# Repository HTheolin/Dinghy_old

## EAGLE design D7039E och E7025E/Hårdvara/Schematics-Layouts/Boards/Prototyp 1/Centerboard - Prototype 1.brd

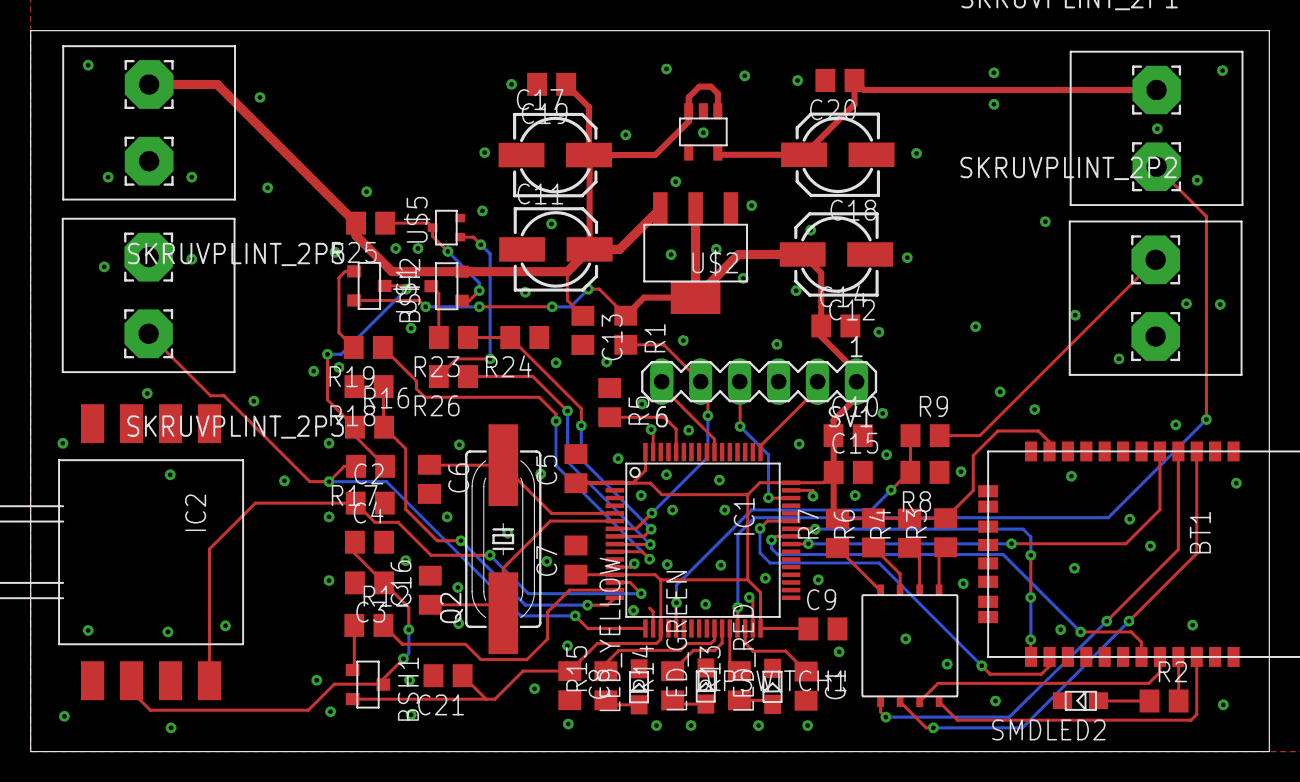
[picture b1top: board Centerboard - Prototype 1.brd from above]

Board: 2 copper layers, 80.8 x 47.0 mm, 62 parts (0 on the bottom side), 49 nets.

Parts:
BSH1, BSH2: ZXMP10A13F; P-CHANNEL
BT1: BLUETOOTH-RN42; RN42
C1: 4u7; C0805
C2: 470pF; C0805
C3: 1uF; C0805
C4: 0.01uF; C0805
C5, C7, C8, C9, C10, C13, C14, C15, C19, C20: 100n; C0805
C6, C16: 25p; C0805
C11, C12, C17, C18: 10u; 153CLV-0505
C21: 1u; C0805
DIPSWITCH1: DIPSWITCH_4P; DIPSWITCH4P
IC1: STM32F401RBT; LQFP64
IC2: MP3V5010; CASE1351
IC3: TPS76150DBVT
LED_GREEN: SMD_LED; SMD_LED_CUSTOM
LED_RED: SMD_LED; SMD_LED_CUSTOM
LED_YELLOW: SMD_LED; SMD_LED_CUSTOM
Q2: 18p; HC49UP
R1, R5, R25: 10k; R0805
R2, R13, R14, R15: 220; R0805
R3, R4, R6, R7, R8, R12, R19, R26: 1k; R0805
R9: 680; R0805
R16, R17, R18: 350; R0805
R23: 6.8k; R0805
R24: 3.3k; R0805
SKRUVPLINT_2P1, SKRUVPLINT_2P2, SKRUVPLINT_2P3, SKRUVPLINT_2P5: SKRUVPLINT_2P
SMDLED2: SMD_LED; SMD_LED_CUSTOM
SV1: MA06-1
U$1: ZXMP10A13F; P-CHANNEL
U$2: LM1117; SOT-223
U$5: SI1330EDL; SOT-323

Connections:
+3V3: BSH1.SOURCE, BSH2.SOURCE, BT1.11, C5.1, C7.1, C8.1, C9.1, C10.1, C12.+, C14.1, C15.1, C21.1, IC1.1, IC1.13, IC1.19, IC1.32, IC1.48, IC1.64, R1.1, R3.2, R4.2, R6.2, R7.2, SV1.1, U$2.OUTPUT, U$2.VOUT
+5V: C18.+, C20.1, IC3.OUT, SKRUVPLINT_2P1.4
BATMEAS_ON/OFF: IC1.9, R26.1
BAT_MEAS: IC1.8, R23.1, R24.2
BT1_CONNSTAT: BT1.19, IC1.41
BT1_GPIO3: BT1.20, DIPSWITCH1.T2
BT1_GPIO4: BT1.22, DIPSWITCH1.T1
BT1_GPIO6: BT1.3, DIPSWITCH1.T3
BT1_GPIO7: BT1.4, DIPSWITCH1.T4
BT1_RESET: BT1.5, IC1.40
BT1_USART1_RX: BT1.14, IC1.43
BT1_USART1_TX: BT1.13, IC1.42
GND: BT1.1, BT1.12, BT1.15, BT1.16, BT1.17, BT1.18, BT1.28, BT1.29, BT1.31, BT1.32, BT1.33, BT1.34, C1.2, C2.2, C3.2, C4.2, C5.2, C6.2, C7.2, C8.2, C9.2, C10.2, C11.-, C12.-, C13.2, C14.2, C15.2, C16.2, C17.-, C18.-, C19.2, C20.2, C21.2, IC1.12, IC1.18, IC1.31, IC1.47, IC1.63, IC2.P$3, IC3.GND, LED_GREEN.2, LED_RED.2, LED_YELLOW.2, R5.1, R8.1, R18.2, R24.1, SKRUVPLINT_2P2.3, SKRUVPLINT_2P3.3, SKRUVPLINT_2P5.4, SMDLED2.2, SV1.3, U$2.GND, U$5.SOURCE
GPIO_ULTRA_INPUT: IC1.21, R8.2, R9.1
GPIO_ULTRA_TRIGGER: IC1.29, SKRUVPLINT_2P1.3
LED_GREEN: IC1.27, R14.2
LED_RED: IC1.28, R13.2
LED_YELLOW: IC1.26, R15.2
unnamed: C1.1, IC1.30
unnamed: IC1.60, R5.2
unnamed: LED_RED.1, R13.1
unnamed: BT1.21, R2.2
unnamed: DIPSWITCH1.B1, R3.1
unnamed: DIPSWITCH1.B2, R4.1
unnamed: DIPSWITCH1.B3, R6.1
unnamed: C6.1, IC1.5, Q2.2
unnamed: C16.1, IC1.6, Q2.1
unnamed: DIPSWITCH1.B4, R7.1
unnamed: R2.1, SMDLED2.1
unnamed: R9.2, SKRUVPLINT_2P2.4
unnamed: BSH1.DRAIN, C3.1, C4.1, IC2.P$2
unnamed: BSH1.GATE, R12.1
unnamed: LED_GREEN.1, R14.1
unnamed: LED_YELLOW.1, R15.1
unnamed: BSH2.DRAIN, R16.1, R17.1
unnamed: BSH2.GATE, R19.2
unnamed: C11.+, C13.1, C17.+, C19.1, IC3.EN, IC3.IN, R25.2, SKRUVPLINT_2P5.3, U$1.SOURCE, U$2.INPUT
unnamed: R23.2, U$1.DRAIN
unnamed: R25.1, U$1.GATE, U$5.DRAIN
unnamed: R26.2, U$5.GATE
NRST: IC1.7, R1.2, SV1.5
PRESSURE_ADC: C2.1, IC1.14, IC2.P$4
PRESSURE_ON/OFF: IC1.15, R12.2
STRAIN_ADC1: IC1.16, R16.2, R18.1
STRAIN_ADC2: IC1.17, R17.2, SKRUVPLINT_2P3.4
STRAIN_ON/OFF: IC1.10, R19.1
SWCLK: IC1.49, SV1.2
SWDIO: IC1.46, SV1.4
SWO: IC1.55, SV1.6

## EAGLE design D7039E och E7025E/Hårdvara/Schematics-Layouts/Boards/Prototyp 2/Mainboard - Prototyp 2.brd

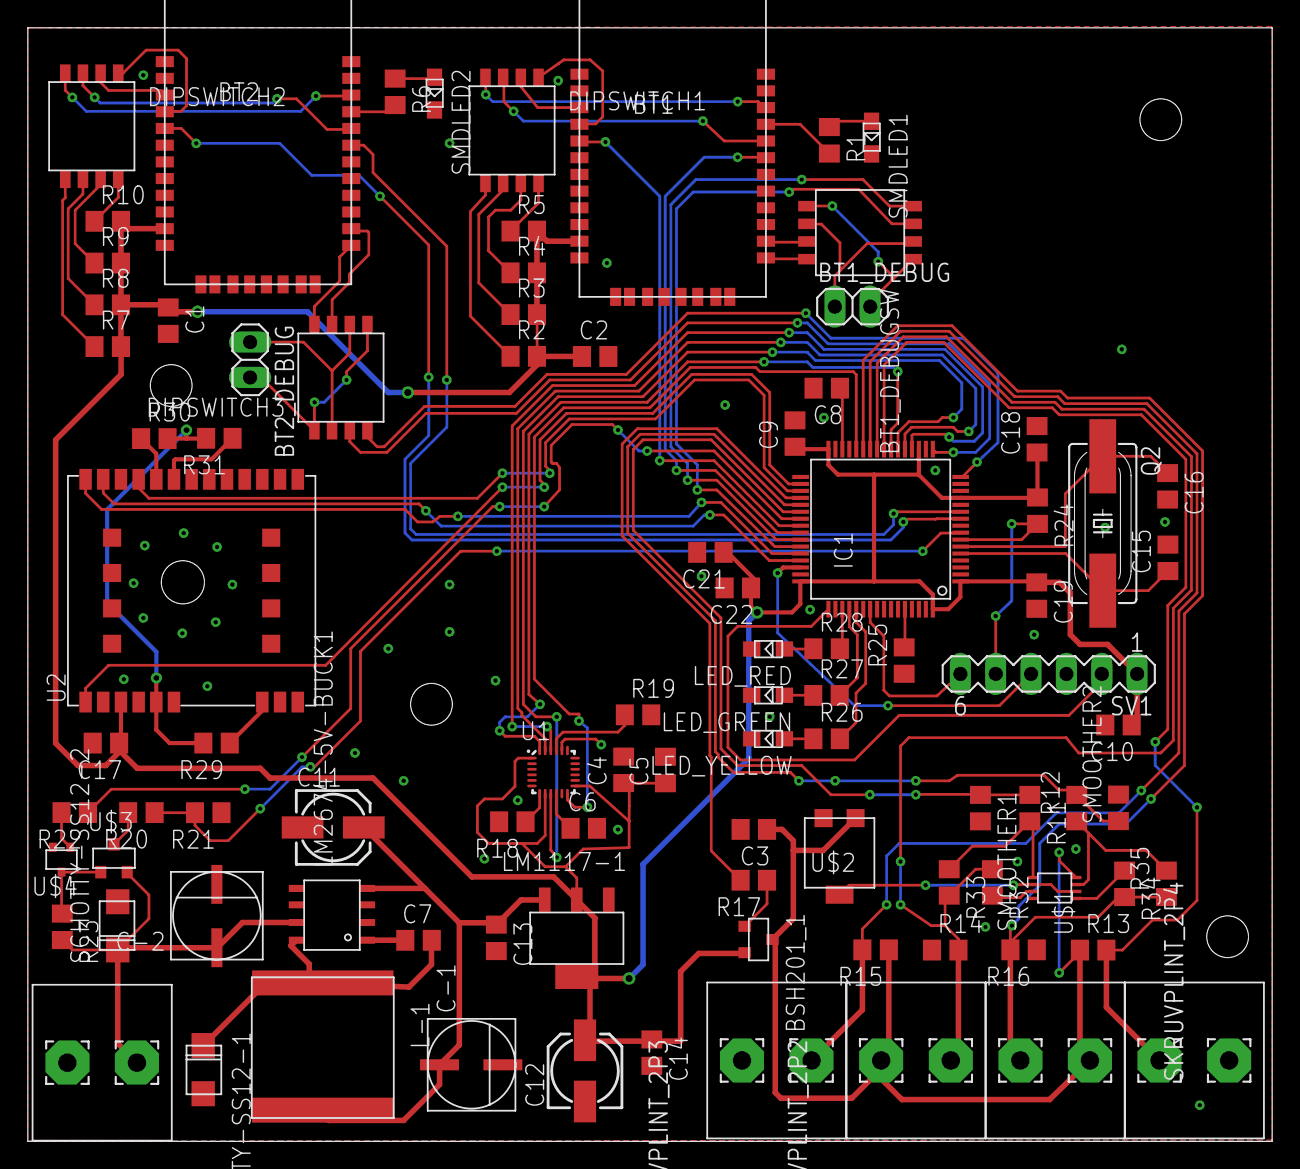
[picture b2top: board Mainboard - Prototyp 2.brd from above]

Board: 2 copper layers, 89.4 x 80.0 mm, 93 parts (0 on the bottom side), 91 nets.

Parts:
BSH201_1: BSH201; P-CHANNEL
BT1, BT2: BLUETOOTH-RN42; RN42
BT1_DEBUG, BT2_DEBUG: 1X02
BT1_DEBUGSW: DIPSWITCH_4P; DIPSWITCH4P
C1, C2, C3, C4, C6, C9, C10, C13, C14, C17, C18, C19, C22: 100n; C0805
C5: 10n; C0805
C7: 0.01uF; C0805
C8: 4u7; C0805
C11, C12: 10u; 153CLV-0505
C15, C16: 25p; C0805
C21: 1u; C0805
C-1, C-2: 100uF; CAP-6.3MM-DIA
DIPSWITCH1, DIPSWITCH2, DIPSWITCH3: DIPSWITCH_4P; DIPSWITCH4P
IC1: STM32F401RBT; LQFP64
L-1: 55uH; INDUCTOR
LED_GREEN: SMD_LED; SMD_LED_CUSTOM
LED_RED: SMD_LED; SMD_LED_CUSTOM
LED_YELLOW: SMD_LED; SMD_LED_CUSTOM
LM1117-1: LM1117
LM2674-5V-BUCK1: LM2674-5VBUCK; LM2674
Q2: 18p; HC49UP
R1, R6, R26, R27, R28: 220; R0805
R2, R3, R4, R5, R7, R8, R9, R10, R11, R12, R22, R32, R34: 1k; R0805
R13, R15: 68; R0805
R14, R16: 4.7k; R0805
R17: 150; R0805
R18, R19: 0; R0805
R20: 6.8k; R0805
R21: 3.3k; R0805
R23, R24, R25, R29, R33, R35: 10k; R0805
R30, R31: 2k2; R0805
SCHOTTY-SS12-1, SCHOTTY-SS12-2: SCHOTTY-SS12; SCHOTTY
SKRUVPLINT_2P1, SKRUVPLINT_2P2, SKRUVPLINT_2P3, SKRUVPLINT_2P4, SKRUVPLINT_2P5: SKRUVPLINT_2P
SMDLED1, SMDLED2: SMD_LED; SMD_LED_CUSTOM
SMOOTHER1, SMOOTHER2: 1n; C0805
SV1: MA06-1
U1: MPU-9250; QFN40P300X300X105-25N
U2: A2235-H; XCVR_A2235-H
U$1: TLV7256; VSSOP
U$2: TS53YL; POT
U$3: ZXMP10A13F; P-CHANNEL
U$4: SI1330EDL; SOT-323

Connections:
1V8_VOUT: R29.2, R30.2, R31.2, U2.5
+3V3: BSH201_1.SOURCE, BT1.11, BT2.11, C1.1, C2.1, C4.1, C5.1, C9.1, C10.1, C12.+, C14.1, C17.1, C18.1, C19.1, C21.1, C22.1, IC1.1, IC1.13, IC1.19, IC1.32, IC1.48, IC1.64, LM1117-1.OUTPUT, LM1117-1.OUTPUT2, R2.2, R3.2, R4.2, R5.2, R7.2, R8.2, R9.2, R10.2, R24.1, SV1.1, U1.1, U1.8, U1.13, U2.3
+5V: C11.+, C13.1, C-1.+, L-1.2, LM1117-1.INPUT, LM2674-5V-BUCK1.4
BATMEAS_TOGGLE: IC1.39, R22.1
BATSUP: C-2.+, LM2674-5V-BUCK1.7, R23.2, SCHOTTY-SS12-2.-, SKRUVPLINT_2P5.3, U$3.SOURCE
BAT_MEAS: IC1.8, R20.1, R21.2
BT1_CONNSTATUS: BT1.19, IC1.41
BT1_DEBUGRX: BT1_DEBUG.2, BT1_DEBUGSW.B1, BT1_DEBUGSW.T4
BT1_DEBUGTX: BT1_DEBUG.1, BT1_DEBUGSW.B2, BT1_DEBUGSW.T3
BT1_GPIO3: BT1.20, DIPSWITCH1.T2
BT1_GPIO4: BT1.22, DIPSWITCH1.T1
BT1_GPIO6: BT1.3, DIPSWITCH1.T3
BT1_GPIO7: BT1.4, DIPSWITCH1.T4
BT1_RESET: BT1.5, IC1.40
BT1_RX: BT1.13, BT1_DEBUGSW.B4
BT1_TX: BT1.14, BT1_DEBUGSW.B3
BT2_CONNSTATUS: BT2.19, IC1.11
BT2_DEBUGRX: BT2_DEBUG.2, DIPSWITCH3.B1, DIPSWITCH3.T4
BT2_DEBUGTX: BT2_DEBUG.1, DIPSWITCH3.B2, DIPSWITCH3.T3
BT2_GPIO3: BT2.20, DIPSWITCH2.T2
BT2_GPIO4: BT2.22, DIPSWITCH2.T1
BT2_GPIO6: BT2.3, DIPSWITCH2.T3
BT2_GPIO7: BT2.4, DIPSWITCH2.T4
BT2_RESET: BT2.5, IC1.10
BT2_RX: BT2.13, DIPSWITCH3.B4
BT2_TX: BT2.14, DIPSWITCH3.B3
GND: BT1.1, BT1.12, BT1.15, BT1.16, BT1.17, BT1.18, BT1.28, BT1.29, BT1.31, BT1.32, BT1.33, BT1.34, BT2.1, BT2.12, BT2.15, BT2.16, BT2.17, BT2.18, BT2.28, BT2.29, BT2.31, BT2.32, BT2.33, BT2.34, C1.2, C2.2, C3.2, C4.2, C5.2, C6.2, C8.2, C9.2, C10.2, C11.-, C12.-, C13.2, C14.2, C15.2, C16.2, C17.2, C18.2, C19.2, C21.2, C22.2, C-1.-, C-2.-, IC1.12, IC1.18, IC1.31, IC1.47, IC1.63, LED_GREEN.2, LED_RED.2, LED_YELLOW.2, LM1117-1.ADJ/GND, LM2674-5V-BUCK1.6, R14.1, R16.1, R18.2, R19.2, R21.1, R25.1, SCHOTTY-SS12-1.+, SCHOTTY-SS12-2.+, SKRUVPLINT_2P1.4, SKRUVPLINT_2P3.4, SKRUVPLINT_2P5.4, SMDLED1.2, SMDLED2.2, SMOOTHER1.2, SMOOTHER2.2, SV1.3, U1.11, U1.18, U1.20, U2.6, U2.9, U2.20, U2.23, U2.24, U2.25, U2.26, U2.27, U2.28, U2.29, U2.30, U$1.P$4, U$2.P$1_A, U$4.SOURCE
GPS_NRST: IC1.34, U2.1
GPS_TOGGLE: IC1.35, U2.19
IMU_INT: IC1.28, U1.12
LED_GREEN: IC1.52, R27.2
LED_RED: IC1.51, R28.2
LED_YELLOW: IC1.53, R26.2
MCURX1_BT1TX: BT1_DEBUGSW.T2, IC1.43
MCURX2_BT2TX: DIPSWITCH3.T2, IC1.17
MCURX6_GPSTX: IC1.45, U2.21
MCUTX1_BT1RX: BT1_DEBUGSW.T1, IC1.42
MCUTX2_BT2RX: DIPSWITCH3.T1, IC1.16
MCUTX6_GPSRX: IC1.44, U2.22
unnamed: BT1.21, R1.2
unnamed: DIPSWITCH1.B1, R2.1
unnamed: DIPSWITCH1.B2, R3.1
unnamed: DIPSWITCH1.B3, R4.1
unnamed: DIPSWITCH1.B4, R5.1
unnamed: BT2.21, R6.2
unnamed: DIPSWITCH2.B1, R7.1
unnamed: DIPSWITCH2.B2, R8.1
unnamed: DIPSWITCH2.B3, R9.1
unnamed: DIPSWITCH2.B4, R10.1
unnamed: R6.1, SMDLED2.1
unnamed: R1.1, SMDLED1.1
unnamed: R11.2, R33.1, U$1.P$1
unnamed: U$1.P$2, U$1.P$6, U$2.P$2_B
unnamed: R12.1, R35.2, U$1.P$7
unnamed: R29.1, U2.7
unnamed: R30.1, U2.18
unnamed: BSH201_1.GATE, R17.1
unnamed: C6.1, U1.10
unnamed: R18.1, U1.7
unnamed: R19.1, U1.21
unnamed: C7.1, LM2674-5V-BUCK1.1
unnamed: R20.2, U$3.DRAIN
unnamed: R22.2, U$4.GATE
unnamed: R23.1, U$3.GATE, U$4.DRAIN
unnamed: C8.1, IC1.30
unnamed: IC1.60, R25.2
unnamed: C15.1, IC1.5, Q2.2
unnamed: C16.1, IC1.6, Q2.1
unnamed: LED_YELLOW.1, R26.1
unnamed: LED_GREEN.1, R27.1
unnamed: R31.1, U2.17
unnamed: LED_RED.1, R28.1
unnamed: R32.2, U$1.P$3
unnamed: R34.1, U$1.P$5
NRST: IC1.7, R24.2, SV1.5
OPTO1_DIODE: IC1.24, R13.2, SKRUVPLINT_2P1.3
OPTO1_OUT: IC1.38, R11.1, SMOOTHER1.1
OPTO1_TRAN: IC1.25, R14.2, R32.1, R33.2, SKRUVPLINT_2P2.3
OPTO2_DIODE: IC1.26, R15.2, SKRUVPLINT_2P3.3
OPTO2_OUT: IC1.37, R12.2, SMOOTHER2.1
OPTO2_TRAN: IC1.27, R16.2, R34.2, R35.1, SKRUVPLINT_2P4.3
OPTO_TOGGLE: IC1.36, R17.2
OPTO_VDD: BSH201_1.DRAIN, C3.1, R13.1, R15.1, SKRUVPLINT_2P2.4, SKRUVPLINT_2P4.4, U$1.P$8, U$2.P$3_C
SPI1_MISO: IC1.22, U1.9
SPI1_MOSI: IC1.23, U1.24
SPI1_NSS: IC1.20, U1.22
SPI1_SCK: IC1.21, U1.23
SWCLK: IC1.49, SV1.2
SWDIO: IC1.46, SV1.4
SWO: IC1.55, SV1.6
VOUT: C7.2, L-1.1, LM2674-5V-BUCK1.8, SCHOTTY-SS12-1.-

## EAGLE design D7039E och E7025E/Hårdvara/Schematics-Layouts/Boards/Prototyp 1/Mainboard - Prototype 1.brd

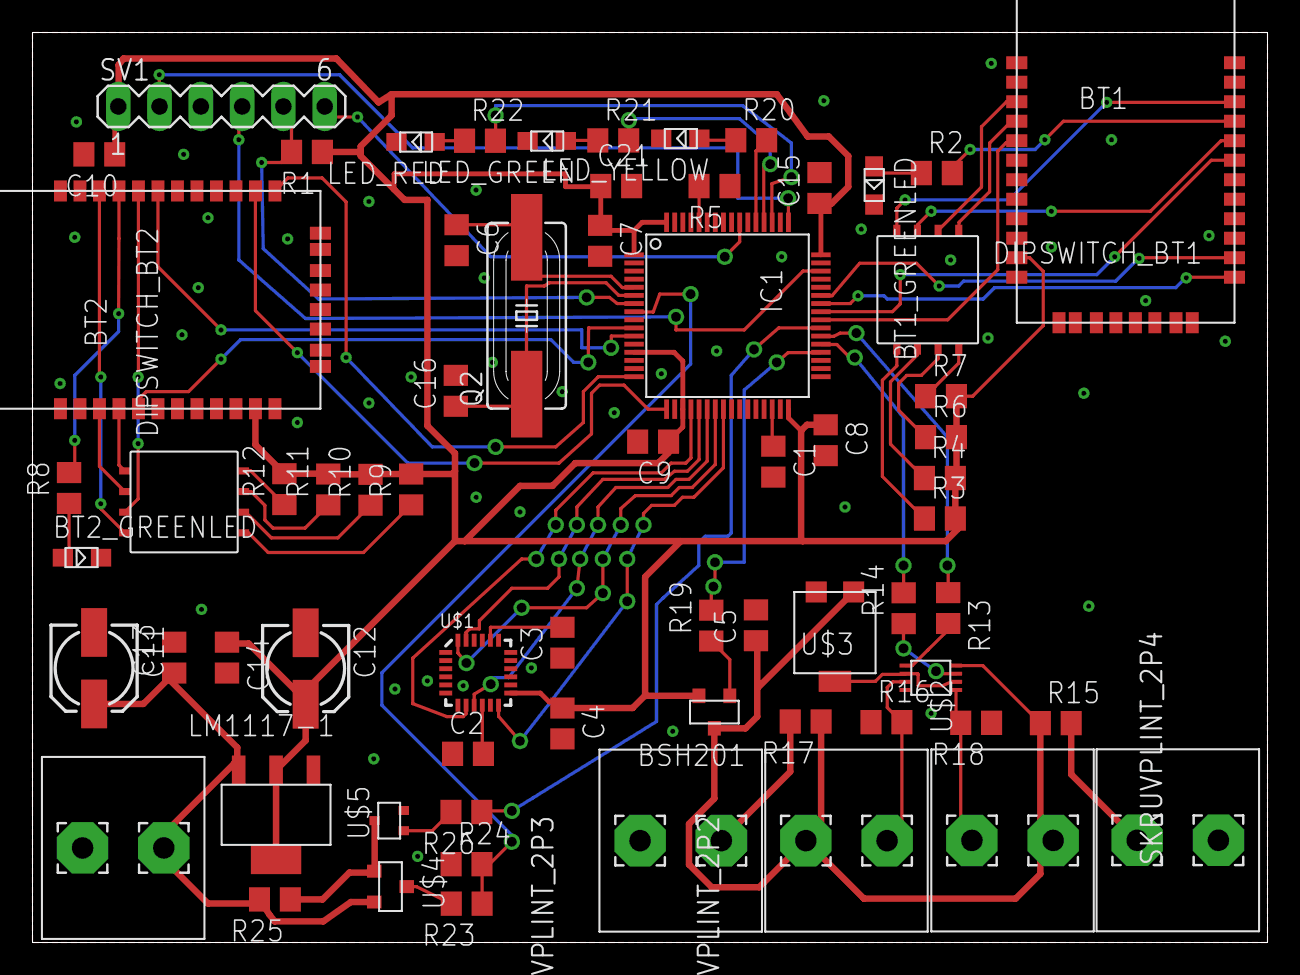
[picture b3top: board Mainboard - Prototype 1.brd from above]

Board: 2 copper layers, 76.0 x 56.0 mm, 67 parts (0 on the bottom side), 69 nets.

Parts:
BSH201: ZXMP10A13F; P-CHANNEL
BT1, BT2: BLUETOOTH-RN42; RN42
BT1_GREENLED, BT2_GREENLED: SMD_LED; SMD_LED_CUSTOM
C1: 4u7; C0805
C2, C4, C5, C7, C8, C9, C10, C13, C14, C15: 100n; C0805
C3: 2.2n; C0805
C6, C16: 25p; C0805
C11, C12: 10u; 153CLV-0505
C21: 1u; C0805
DIPSWITCH_BT1, DIPSWITCH_BT2: DIPSWITCH_4P; DIPSWITCH4P
IC1: STM32F401RBT; LQFP64
LED_GREEN: SMD_LED; SMD_LED_CUSTOM
LED_RED: SMD_LED; SMD_LED_CUSTOM
LED_YELLOW: SMD_LED; SMD_LED_CUSTOM
LM1117-1: LM1117
Q2: 18p; HC49UP
R1, R5, R25: 10k; R0805
R2, R8, R20, R21, R22: 220; R0805
R3, R4, R6, R7, R9, R10, R11, R12, R13, R14, R26: 1k; R0805
R15, R17, R19: 150; R0805
R16, R18: 68; R0805
R23: 6.8k; R0805
R24: 3.3k; R0805
SKRUVPLINT_2P1, SKRUVPLINT_2P2, SKRUVPLINT_2P3, SKRUVPLINT_2P4, SKRUVPLINT_2P5: SKRUVPLINT_2P
SV1: MA06-1
U$1: MPU-6000; QFN-24
U$2: TLV7256; VSSOP
U$3: TS53YL; POT
U$4: ZXMP10A13F; P-CHANNEL
U$5: SI1330EDL; SOT-323

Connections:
1PHOTO: R16.2, SKRUVPLINT_2P2.3, U$2.P$3
2PHOTO: R18.2, SKRUVPLINT_2P4.3, U$2.P$5
+3V3: BSH201.SOURCE, BT1.11, BT2.11, C4.1, C7.1, C8.1, C9.1, C10.1, C12.+, C14.1, C15.1, C21.1, IC1.1, IC1.13, IC1.19, IC1.32, IC1.48, IC1.64, LM1117-1.OUTPUT, LM1117-1.OUTPUT2, R1.1, R3.2, R4.2, R6.2, R7.2, R9.2, R10.2, R11.2, R12.2, SV1.1, U$1.13
BATMEAS_TOGGLE: IC1.39, R26.1
BAT_MEAS: IC1.8, R23.1, R24.2
BT1_CONNSTAT: BT1.19, IC1.41
BT1_GPIO3: BT1.20, DIPSWITCH_BT1.T2
BT1_GPIO4: BT1.22, DIPSWITCH_BT1.T1
BT1_GPIO6: BT1.3, DIPSWITCH_BT1.T3
BT1_GPIO7: BT1.4, DIPSWITCH_BT1.T4
BT1_RESET: BT1.5, IC1.40
BT1_USART1_RX: BT1.14, IC1.43
BT1_USART1_TX: BT1.13, IC1.42
BT2_CONNSTAT: BT2.19, IC1.11
BT2_GPIO3: BT2.20, DIPSWITCH_BT2.T2
BT2_GPIO4: BT2.22, DIPSWITCH_BT2.T1
BT2_GPIO5: BT2.21, R8.2
BT2_GPIO6: BT2.3, DIPSWITCH_BT2.T3
BT2_GPIO7: BT2.4, DIPSWITCH_BT2.T4
BT2_RESET: BT2.5, IC1.10
BT2_USART2_RX: BT2.14, IC1.17
BT2_USART2_TX: BT2.13, IC1.16
GND: BT1.1, BT1.12, BT1.15, BT1.16, BT1.17, BT1.18, BT1.28, BT1.29, BT1.31, BT1.32, BT1.33, BT1.34, BT1_GREENLED.2, BT2.1, BT2.12, BT2.15, BT2.16, BT2.17, BT2.18, BT2.28, BT2.29, BT2.31, BT2.32, BT2.33, BT2.34, BT2_GREENLED.2, C1.2, C2.1, C3.1, C4.2, C5.2, C6.2, C7.2, C8.2, C9.2, C10.2, C11.-, C12.-, C13.2, C14.2, C15.2, C16.2, C21.2, IC1.12, IC1.18, IC1.31, IC1.47, IC1.63, LED_GREEN.2, LED_RED.2, LED_YELLOW.2, LM1117-1.ADJ/GND, R5.1, R16.1, R18.1, R24.1, SKRUVPLINT_2P1.4, SKRUVPLINT_2P3.4, SKRUVPLINT_2P5.4, SV1.3, U$1.1, U$1.6, U$1.7, U$1.11, U$1.18, U$2.P$4, U$3.P$1_A, U$5.SOURCE
LED_GREEN: IC1.52, R21.2
LED_RED: IC1.51, R22.2
LED_YELLOW: IC1.53, R20.2
MPU_INT: IC1.24, U$1.12
unnamed: C1.1, IC1.30
unnamed: IC1.60, R5.2
unnamed: R13.2, U$2.P$1
unnamed: BT1.21, R2.2
unnamed: DIPSWITCH_BT1.B1, R3.1
unnamed: DIPSWITCH_BT1.B2, R4.1
unnamed: DIPSWITCH_BT1.B3, R6.1
unnamed: C6.1, IC1.5, Q2.2
unnamed: C16.1, IC1.6, Q2.1
unnamed: DIPSWITCH_BT1.B4, R7.1
unnamed: BT1_GREENLED.1, R2.1
unnamed: DIPSWITCH_BT2.B1, R9.1
unnamed: DIPSWITCH_BT2.B2, R10.1
unnamed: DIPSWITCH_BT2.B3, R11.1
unnamed: DIPSWITCH_BT2.B4, R12.1
unnamed: BT2_GREENLED.1, R8.1
unnamed: C2.2, U$1.10
unnamed: C3.2, U$1.20
unnamed: U$2.P$2, U$2.P$6, U$3.P$2_B
unnamed: R14.1, U$2.P$7
unnamed: R15.2, SKRUVPLINT_2P1.3
unnamed: R17.2, SKRUVPLINT_2P3.3
unnamed: BSH201.GATE, R19.1
unnamed: R23.2, U$4.DRAIN
unnamed: R25.1, U$4.GATE, U$5.DRAIN
unnamed: R26.2, U$5.GATE
unnamed: LED_YELLOW.1, R20.1
unnamed: LED_GREEN.1, R21.1
unnamed: LED_RED.1, R22.1
NRST: IC1.7, R1.2, SV1.5
PHOTO1_OUT: IC1.38, R13.1
PHOTO2_OUT: IC1.37, R14.2
PHOTOMEAS_TOGGLE: IC1.36, R19.2
PHOTOVDD: BSH201.DRAIN, C5.1, R15.1, R17.1, SKRUVPLINT_2P2.4, SKRUVPLINT_2P4.4, U$2.P$8, U$3.P$3_C
SPI1_MISO: IC1.22, U$1.9
SPI1_MOSI: IC1.23, U$1.24
SPI1_NSS: IC1.20, U$1.8
SPI1_SCK: IC1.21, U$1.23
SWCLK: IC1.49, SV1.2
SWDIO: IC1.46, SV1.4
SWO: IC1.55, SV1.6
VREGIN: C11.+, C13.1, LM1117-1.INPUT, R25.2, SKRUVPLINT_2P5.3, U$4.SOURCE

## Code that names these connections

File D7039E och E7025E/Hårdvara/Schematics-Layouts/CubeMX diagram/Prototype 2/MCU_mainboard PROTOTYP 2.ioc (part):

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Mcu.Name=STM32F401R(D-E)Tx
Mcu.Package=LQFP64
Mcu.UserName=STM32F401RETx
PA10.GPIOParameters=GPIO_Label
PA10.GPIO_Label=BT1_USART1RX
PA10.Mode=Asynchronous
PA10.Signal=USART1_RX
PA11.GPIOParameters=GPIO_Label
PA11.GPIO_Label=GPS_USART6TX
PA11.Mode=Asynchronous
PA11.Signal=USART6_TX
PA12.GPIOParameters=GPIO_Label
PA12.GPIO_Label=GPS_USART6RX
PA12.Mode=Asynchronous
PA12.Signal=USART6_RX
PA13.Mode=Trace_Asynchronous_SW
PA13.Signal=SYS_JTMS-SWDIO
PA14.Mode=Trace_Asynchronous_SW
PA14.Signal=SYS_JTCK-SWCLK
PA2.GPIOParameters=GPIO_Label
PA2.GPIO_Label=BT2_USART2TX
PA2.Mode=Asynchronous
PA2.Signal=USART2_TX
PA3.GPIOParameters=GPIO_Label
PA3.GPIO_Label=BT2_USART2RX
PA3.Mode=Asynchronous
PA3.Signal=USART2_RX
PA4.Mode=NSS_Signal_Hard_Output
PA4.Signal=SPI1_NSS
PA5.Mode=Full_Duplex_Master
PA5.Signal=SPI1_SCK
PA6.Mode=Full_Duplex_Master
PA6.Signal=SPI1_MISO
PA7.Mode=Full_Duplex_Master
PA7.Signal=SPI1_MOSI
PA8.GPIOParameters=GPIO_Label
PA8.GPIO_Label=BT1_CONNSTAT
PA8.Signal=GPIO_Input
PA9.GPIOParameters=GPIO_Label
PA9.GPIO_Label=BT1_USART1TX
PA9.Mode=Asynchronous
PA9.Signal=USART1_TX
PB0.GPIOParameters=GPIO_Label
PB0.GPIO_Label=Opto 2 Diode Failure
PB0.Signal=ADCx_IN8
PB1.GPIOParameters=GPIO_Label
PB1.GPIO_Label=Opto 2 Transistor Failure
PB1.Signal=ADCx_IN9
PB13.GPIOParameters=GPIO_Label
PB13.GPIO_Label=GPS_NRST
PB13.Signal=GPIO_Output
PB14.GPIOParameters=GPIO_Label
PB14.GPIO_Label=GPS_TOGGLE
PB14.Signal=GPIO_Output
PB15.GPIOParameters=GPIO_Label
PB15.GPIO_Label=OPTO_TOGGLE
PB15.Signal=GPIO_Output
PB2.GPIOParameters=GPIO_Label
PB2.GPIO_Label=MPU_INT
PB2.Signal=GPIO_Input
PB3.Mode=Trace_Asynchronous_SW
PB3.Signal=SYS_JTDO-SWO
PC0.GPIOParameters=GPIO_Label
PC0.GPIO_Label=BAT_MEAS
PC0.Signal=ADCx_IN10
PC10.GPIOParameters=GPIO_Label
PC10.GPIO_Label=LED_RED
PC10.Signal=GPIO_Output
PC11.GPIOParameters=GPIO_Label
PC11.GPIO_Label=LED_GREEN
PC11.Signal=GPIO_Output
PC12.GPIOParameters=GPIO_Label
PC12.GPIO_Label=LED_YELLOW
PC12.Signal=GPIO_Output
PC2.GPIOParameters=GPIO_Label
PC2.GPIO_Label=BT2_RESET
PC2.Signal=GPIO_Output
PC3.GPIOParameters=GPIO_Label
PC3.GPIO_Label=BT2_CONNSTAT
PC3.Signal=GPIO_Input
PC4.GPIOParameters=GPIO_Label
PC4.GPIO_Label=Opto 1 Diode Failure
PC4.Signal=ADCx_IN14
PC5.GPIOParameters=GPIO_Label
PC5.GPIO_Label=Opto 1 TransistorFailure
PC5.Signal=ADCx_IN15
PC6.GPIOParameters=GPIO_Label
PC6.GPIO_Label=OPTO2_OUT
PC6.Signal=GPIO_Input
PC7.GPIOParameters=GPIO_Label
PC7.GPIO_Label=OPTO1_OUT
PC7.Signal=GPIO_Input
PC8.GPIOParameters=GPIO_Label
PC8.GPIO_Label=BATMEAS_TOGGLE
PC8.Signal=GPIO_Output
PC9.GPIOParameters=GPIO_Label
PC9.GPIO_Label=BT1_RESET
PC9.Signal=GPIO_Output
RCC.HSE_VALUE=25000000
RCC.SYSCLKFreq_VALUE=16000000

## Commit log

2017-08-29 :lollipop: Added .gitattributes
2017-08-30 Old stuff
